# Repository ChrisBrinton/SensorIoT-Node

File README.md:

# SensorIoT-Node (Deprecated)

> **This repository has been consolidated into [SensorIoT-GW](https://github.com/ChrisBrinton/SensorIoT-GW).**
>
> All sensor node firmware and PCB designs now live under `firmware/node/` and `PCBs/node/` in the consolidated repo.
> This repository is kept for historical reference only.

## Original Description
# SensorIoT-Node
The sensor nodes for the SensorIoT environment

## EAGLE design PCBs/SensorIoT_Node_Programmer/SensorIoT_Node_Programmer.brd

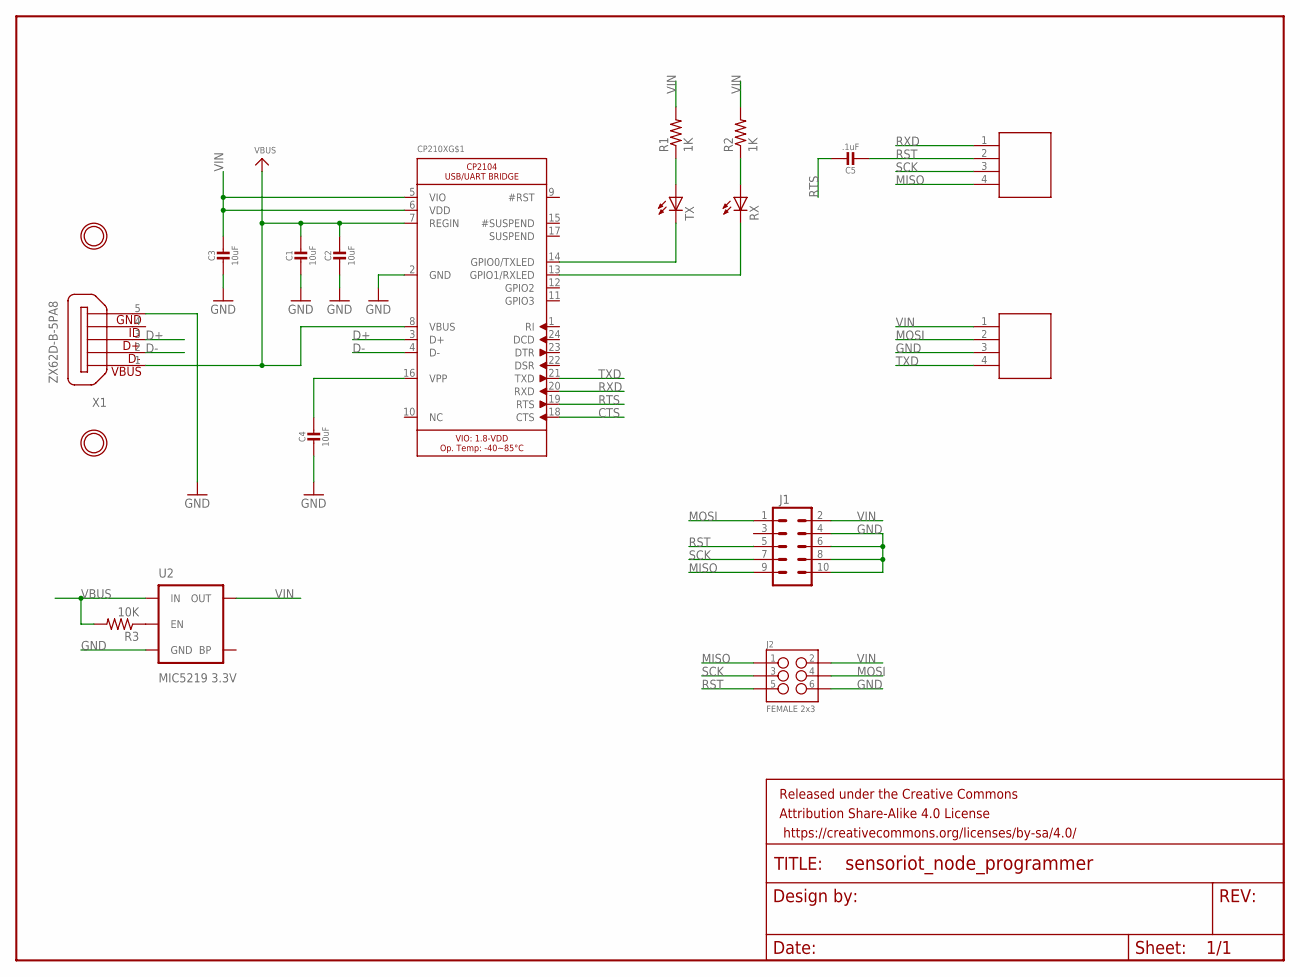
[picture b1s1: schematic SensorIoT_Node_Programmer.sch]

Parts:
C1, C2, C3, C4: 10uF; _0805
C5: .1uF; _0805
CP210X: CP2104; QFN24_4MM_SMSC
FRAME1: FRAME-LETTER; CREATIVE_COMMONS
J1: M05X2PTH; AVR_ICSP
J2: FEMALE 2x3; 2X3
R1, R2: 1K; 0805
R3: 10K; 0805
RX: LEDCHIP-LED0805; CHIP-LED0805
TX: LEDCHIP-LED0805; CHIP-LED0805
U2: MIC5219 3.3V; SOT23-5
U$2, U$3: MOUNTINGHOLE2.0; MOUNTINGHOLE_2.0_PLATED
U$4, U$5: 4X.1IN_POGO_PIN
X1: ZX62D-B-5PA8

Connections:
CTS: CP210X.18 (CTS)
D+: CP210X.3 (D+), X1.3
D-: CP210X.4 (D-), X1.2
GND: C1.2, C2.2, C3.2, C4.2, CP210X.2 (GND), J1.4, J1.6, J1.8, J1.10, J2.6, U2.2 (GND), U$5.3, X1.5
MISO: J1.9, J2.1, U$4.4
MOSI: J1.1, J2.4, U$5.2
unnamed: C4.1, CP210X.16 (VPP)
unnamed: CP210X.14 (GPIO0/TXLED), TX.C
unnamed: R3.1, U2.3 (EN)
unnamed: CP210X.13 (GPIO1/RXLED), RX.C
unnamed: R1.1, TX.A
unnamed: R2.1, RX.A
RST: C5.2, J1.5, J2.5, U$4.2
RTS: C5.1, CP210X.19 (RTS)
RXD: CP210X.20 (RXD), U$4.1
SCK: J1.7, J2.3, U$4.3
TP: CP210X.THERM (TP)
TXD: CP210X.21 (TXD), U$5.4
VBUS: C1.1, C2.1, CP210X.7 (REGIN), CP210X.8 (VBUS), R3.2, U2.1 (IN), X1.1
VIN: C3.1, CP210X.5 (VIO), CP210X.6 (VDD), J1.2, J2.2, R1.2, R2.2, U2.5 (OUT), U$5.1

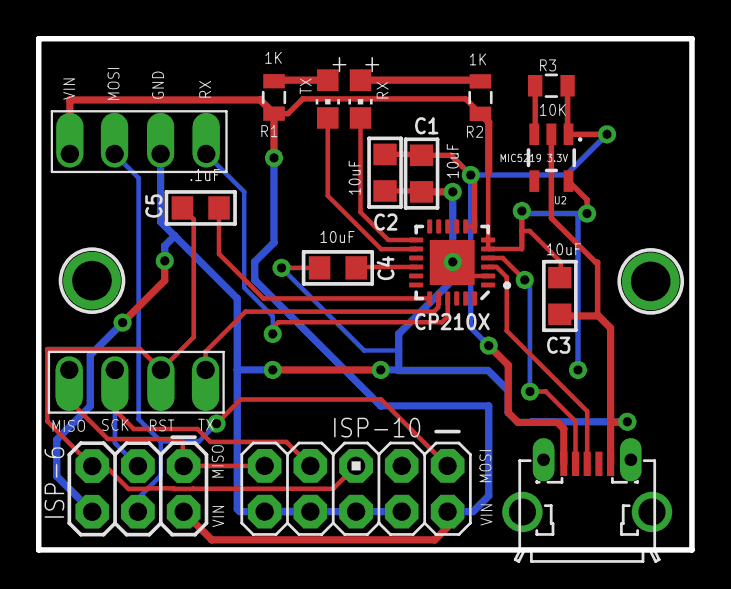
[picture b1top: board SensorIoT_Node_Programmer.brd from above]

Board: 2 copper layers, 36.3 x 28.4 mm, 20 parts (0 on the bottom side), 18 nets.

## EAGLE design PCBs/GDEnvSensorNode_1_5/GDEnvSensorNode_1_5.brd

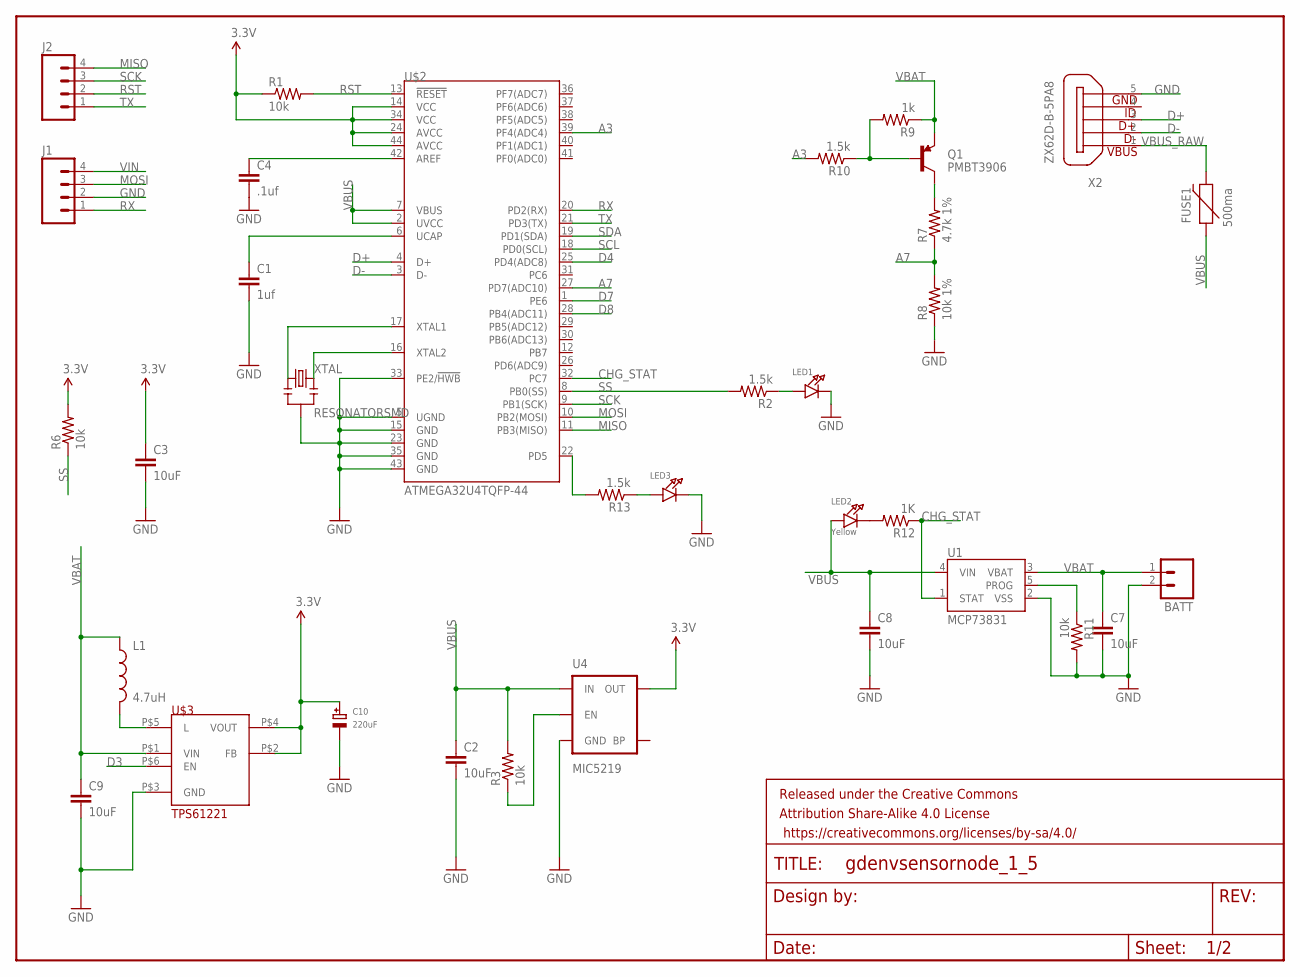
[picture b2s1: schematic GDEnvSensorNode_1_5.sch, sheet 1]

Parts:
BATT: M02JST-PTH-2; JST-2-PTH
C1: 1uf; 0805
C2, C3, C7, C8, C9: 10uF; 0805
C4: .1uf; 0805
C10: 220uF; EIA3528-21/B-R
FRAME1: FRAME-LETTER; CREATIVE_COMMONS
FUSE1: 500ma; PTC-1206
J1, J2: M04PTH; 1X04
L1: 4.7uH; 1210
LED1, LED3: LED0805; CHIPLED_0805
LED2: Yellow; CHIPLED_0805
Q1: PMBT3906; SOT23-3
R1, R3, R6, R11: 10k; 0805
R2, R10, R13: 1.5k; 0805
R7: 4.7k 1%; 0805
R8: 10k 1%; 0805
R9: 1k; 0805
R12: 1K; 0805
U1: MCP73831; SOT23-5
U4: MIC5219; SOT23-5
U$2: ATMEGA32U4TQFP-44; TQFP44
U$3: TPS61221
X2: ZX62D-B-5PA8
XTAL: RESONATORSMD; RESONATOR-SMD

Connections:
A3: R10.2, U$2.39 (PF4(ADC4))
A7: R7.1, R8.2, U$2.27 (PD7(ADC10))
CHG_STAT: R12.1, U1.1 (STAT), U$2.32 (PC7)
D3: U$3.P$6 (EN)
D4: U$2.25 (PD4(ADC8)); also elsewhere on the board
D7: U$2.1 (PE6); also elsewhere on the board
D8: U$2.28 (PB4(ADC11)); also elsewhere on the board
D+: U$2.4 (D+), X2.3
D-: U$2.3 (D-), X2.2
GND: BATT.2, C1.2, C2.2, C3.2, C4.2, C7.2, C8.2, C9.2, C10.-, J1.2, LED1.C, LED3.C, R8.1, R11.2, U1.2 (VSS), U4.2 (GND), U$2.5 (UGND), U$2.15 (GND), U$2.23 (GND), U$2.33 (PE2/!HWB), U$2.35 (GND), U$2.43 (GND), U$3.P$3 (GND), X2.5, XTAL.2; also elsewhere on the board
L: L1.2, U$3.P$5 (L)
MISO: J2.4, U$2.11 (PB3(MISO)); also elsewhere on the board
MOSI: J1.3, U$2.10 (PB2(MOSI)); also elsewhere on the board
unnamed: U$2.16 (XTAL2), XTAL.3
unnamed: U$2.17 (XTAL1), XTAL.1
unnamed: LED1.A, R2.1
unnamed: LED2.C, R12.2
unnamed: C4.1, U$2.42 (AREF)
unnamed: LED3.A, R13.1
unnamed: R3.1, U4.3 (EN)
unnamed: Q1.1 (B), R9.2, R10.1
unnamed: Q1.3 (C), R7.2
unnamed: R13.2, U$2.22 (PD5)
unnamed: R11.1, U1.5 (PROG)
unnamed: C1.1, U$2.6 (UCAP)
RST: J2.2, R1.2, U$2.13 (!RESET)
RX: J1.1, U$2.20 (PD2(RX))
SCK: J2.3, U$2.9 (PB1(SCK)); also elsewhere on the board
SCL: U$2.18 (PD0(SCL)); also elsewhere on the board
SDA: U$2.19 (PD1(SDA)); also elsewhere on the board
SS: R2.2, R6.1, U$2.8 (PB0(SS))
TX: J2.1, U$2.21 (PD3(TX))
VBAT: BATT.1, C7.1, C9.1, L1.1, Q1.2 (E), R9.1, U1.3 (VBAT), U$3.P$1 (VIN)
VBUS: C2.1, C8.1, FUSE1.1, LED2.A, R3.2, U1.4 (VIN), U4.1 (IN), U$2.2 (UVCC), U$2.7 (VBUS)
VBUS_RAW: FUSE1.2, X2.1
VIN: J1.4

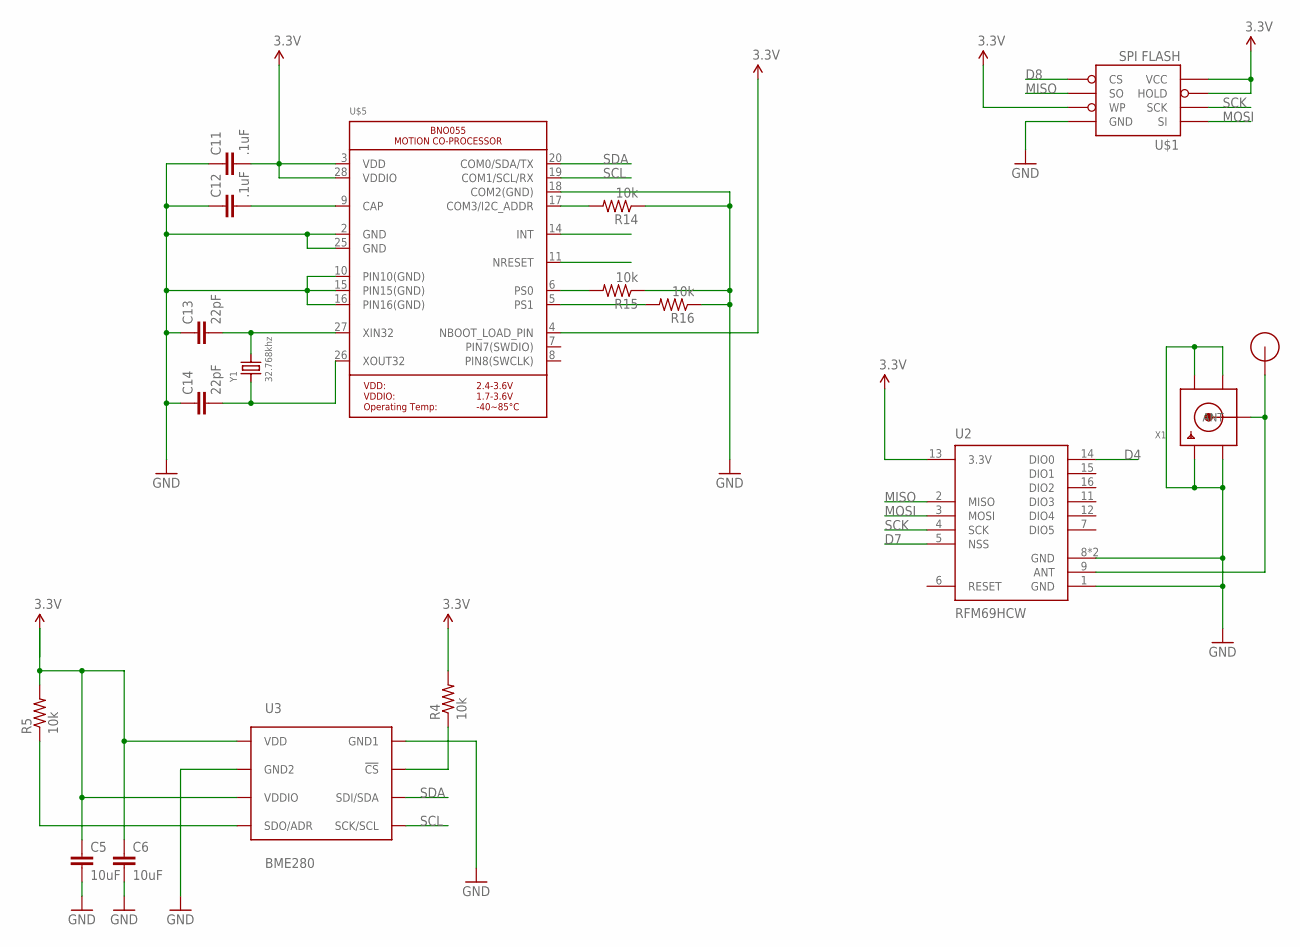
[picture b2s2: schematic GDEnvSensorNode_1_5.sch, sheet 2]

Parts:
C5, C6: 10uF; 0805
C11, C12: .1uF; 0805
C13, C14: 22pF; 0805
R4, R5, R14, R15, R16: 10k; 0805
U2: RFM69HCW; RFM69HCW-XXXS2
U3: BME280; BME280_LGA
U$1: SPI FLASH; SO08
U$4: RFM12B_ANTENNA; RFM12B-ANTENNA
U$5: MICROBUILDER_BNO055
X1: SMACONNECTOR_EDGE_UFL; SMA_EDGELAUNCH_UFL
Y1: 32.768khz; CRYSTAL_8X3.8

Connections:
ANT: U2.9 (ANT), U$4.P$1, X1.P (ANT)
D4: U2.14 (DIO0); also elsewhere on the board
D7: U2.5 (NSS); also elsewhere on the board
D8: U$1.1_CS (CS); also elsewhere on the board
GND: C5.2, C6.2, C11.1, C12.1, C13.1, C14.1, R14.1, R15.1, R16.1, U2.1 (GND), U2.8 (GND), U2.10 (GND), U3.P$1 (GND1), U3.P$7 (GND2), U$1.4_GND (GND), U$5.2 (GND), U$5.10 (PIN10(GND)), U$5.15 (PIN15(GND)), U$5.16 (PIN16(GND)), U$5.18 (COM2(GND)), U$5.25 (GND), X1.GND@1 (GND1), X1.GND@2 (GND2), X1.GND@3 (GND3), X1.GND@4 (GND4); also elsewhere on the board
MISO: U2.2 (MISO), U$1.2_SO (SO); also elsewhere on the board
MOSI: U2.3 (MOSI), U$1.5_SI (SI); also elsewhere on the board
unnamed: R4.1, U3.P$2 (!CS)
unnamed: C12.2, U$5.9 (CAP)
unnamed: C5.1, C6.1, R5.2, U3.P$6 (VDDIO), U3.P$8 (VDD)
unnamed: R5.1, U3.P$5 (SDO/ADR)
unnamed: C13.2, U$5.27 (XIN32), Y1.P$4 (2)
unnamed: C14.2, U$5.26 (XOUT32), Y1.P$1 (1)
unnamed: R14.2, U$5.17 (COM3/I2C_ADDR)
unnamed: R15.2, U$5.6 (PS0)
unnamed: R16.2, U$5.5 (PS1)
SCK: U2.4 (SCK), U$1.6_SCK (SCK); also elsewhere on the board
SCL: U3.P$4 (SCK/SCL), U$5.19 (COM1/SCL/RX); also elsewhere on the board
SDA: U3.P$3 (SDI/SDA), U$5.20 (COM0/SDA/TX); also elsewhere on the board

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
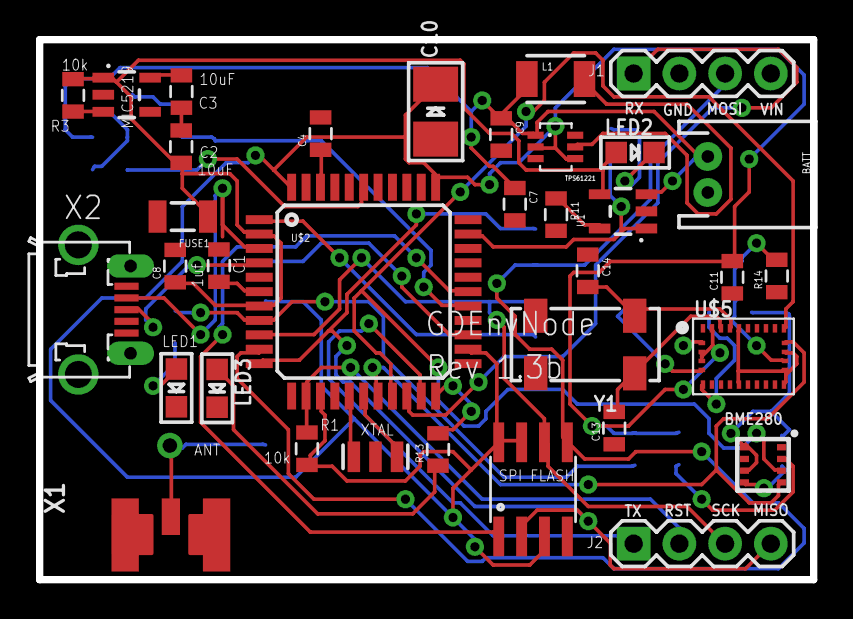
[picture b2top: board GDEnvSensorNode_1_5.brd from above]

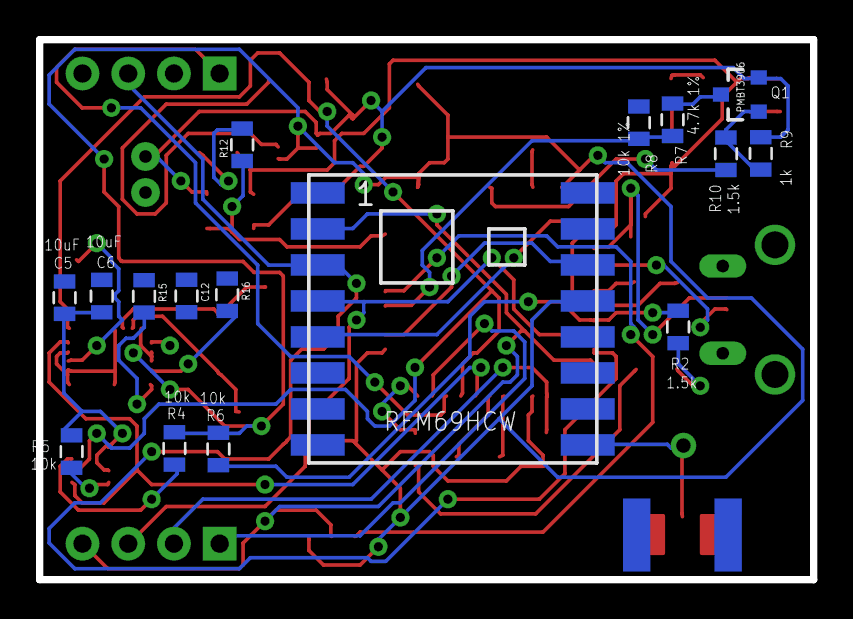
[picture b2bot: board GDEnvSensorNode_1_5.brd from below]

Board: 2 copper layers, 43.0 x 30.0 mm, 53 parts (16 on the bottom side), 46 nets.

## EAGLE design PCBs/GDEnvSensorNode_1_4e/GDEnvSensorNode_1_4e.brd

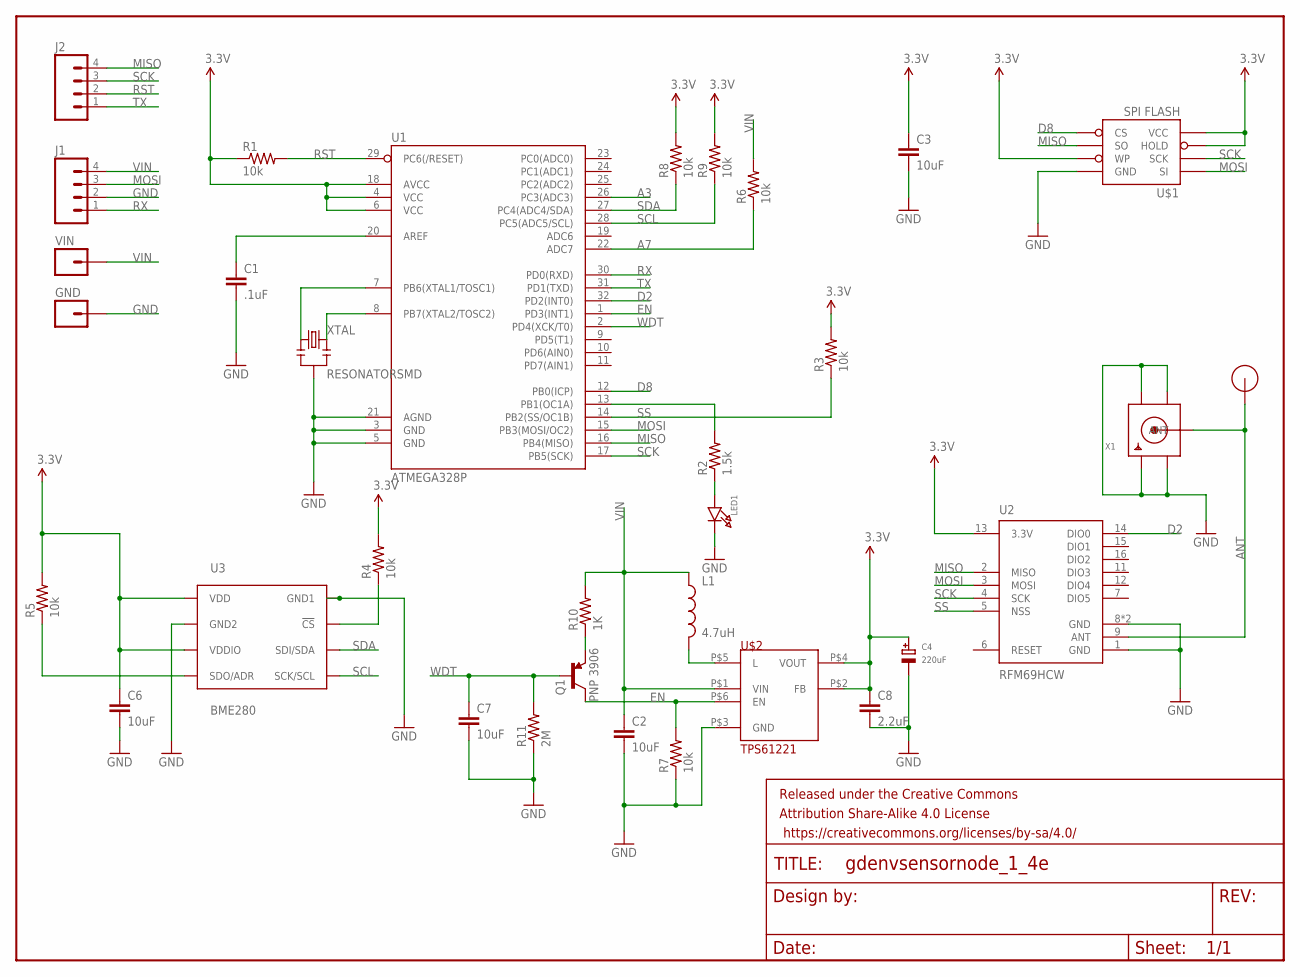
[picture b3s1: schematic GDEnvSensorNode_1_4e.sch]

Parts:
C1: .1uF; 0805
C2, C3, C6, C7: 10uF; 0805
C4: 220uF; EIA7343-31/D-R
C8: 2.2uF; 0805
FRAME1: FRAME-LETTER; CREATIVE_COMMONS
GND: M01PTH_2MM; 1X01_2MM
J1, J2: M04PTH; 1X04
L1: 4.7uH; 1210
LED1: LED0805; CHIPLED_0805
Q1: PNP 3906; SOT23-3
R1, R3, R4, R5, R6, R7, R8, R9: 10k; 0805
R2: 1.5k; 0805
R10: 1K; R0805
R11: 2M; R0805
U1: ATMEGA328P; TQFP32-08
U2: RFM69HCW; RFM69HCW-XXXS2
U3: BME280; BME280_LGA
U$1: SPI FLASH; SO08
U$2: TPS61221
U$4: RFM12B_ANTENNA; RFM12B-ANTENNA
VIN: M01PTH_2MM; 1X01_2MM
X1: SMACONNECTOR_EDGE_UFL; SMA_EDGELAUNCH_UFL
XTAL: RESONATORSMD; RESONATOR-SMD

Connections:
3.3V: C3.1, C4.+, C6.1, C8.1, R1.1, R3.2, R4.2, R5.2, R8.2, R9.2, U1.4 (VCC), U1.6 (VCC), U1.18 (AVCC), U2.13 (3.3V), U3.P$6 (VDDIO), U3.P$8 (VDD), U$1.3_WP (WP), U$1.7_HOLD (HOLD), U$1.8_VCC (VCC), U$2.P$2 (FB), U$2.P$4 (VOUT)
A3: U1.26 (PC3(ADC3))
A7: R6.1, U1.22 (ADC7)
ANT: U2.9 (ANT), U$4.P$1, X1.P (ANT)
D2: U1.32 (PD2(INT0)), U2.14 (DIO0)
D8: U1.12 (PB0(ICP)), U$1.1_CS (CS)
EN: Q1.3 (C), R7.2, U1.1 (PD3(INT1)), U$2.P$6 (EN)
GND: C1.2, C2.2, C3.2, C4.-, C6.2, C7.2, C8.2, GND.1, J1.2, LED1.C, R7.1, R11.1, U1.3 (GND), U1.5 (GND), U1.21 (AGND), U2.1 (GND), U2.8 (GND), U2.10 (GND), U3.P$1 (GND1), U3.P$7 (GND2), U$1.4_GND (GND), U$2.P$3 (GND), X1.GND@1 (GND1), X1.GND@2 (GND2), X1.GND@3 (GND3), X1.GND@4 (GND4), XTAL.2
L: L1.2, U$2.P$5 (L)
MISO: J2.4, U1.16 (PB4(MISO)), U2.2 (MISO), U$1.2_SO (SO)
MOSI: J1.3, U1.15 (PB3(MOSI/OC2)), U2.3 (MOSI), U$1.5_SI (SI)
unnamed: U1.8 (PB7(XTAL2/TOSC2)), XTAL.3
unnamed: U1.7 (PB6(XTAL1/TOSC1)), XTAL.1
unnamed: LED1.A, R2.1
unnamed: Q1.2 (E), R10.1
unnamed: R4.1, U3.P$2 (!CS)
unnamed: R2.2, U1.13 (PB1(OC1A))
unnamed: C1.1, U1.20 (AREF)
unnamed: R5.1, U3.P$5 (SDO/ADR)
RST: J2.2, R1.2, U1.29 (PC6(/RESET))
RX: J1.1, U1.30 (PD0(RXD))
SCK: J2.3, U1.17 (PB5(SCK)), U2.4 (SCK), U$1.6_SCK (SCK)
SCL: R9.1, U1.28 (PC5(ADC5/SCL)), U3.P$4 (SCK/SCL)
SDA: R8.1, U1.27 (PC4(ADC4/SDA)), U3.P$3 (SDI/SDA)
SS: R3.1, U1.14 (PB2(SS/OC1B)), U2.5 (NSS)
TX: J2.1, U1.31 (PD1(TXD))
VIN: C2.1, J1.4, L1.1, R6.2, R10.2, U$2.P$1 (VIN), VIN.1
WDT: C7.1, Q1.1 (B), R11.2, U1.2 (PD4(XCK/T0))

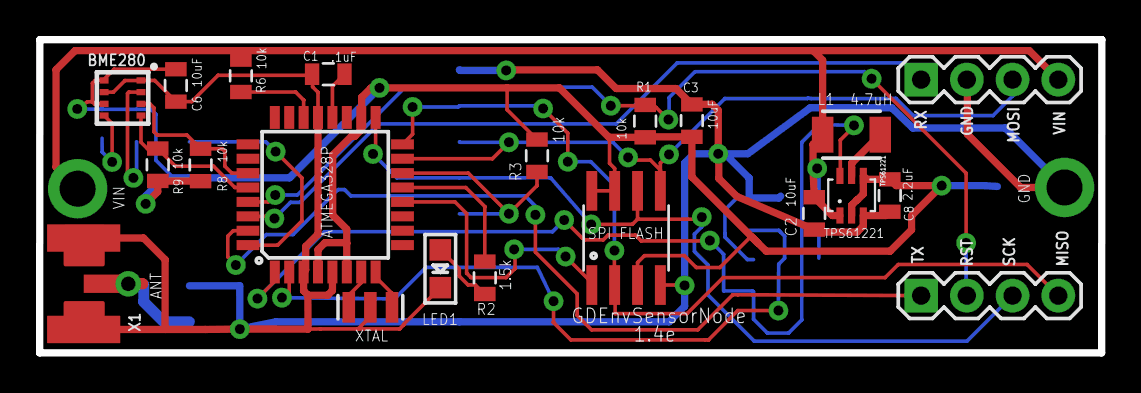
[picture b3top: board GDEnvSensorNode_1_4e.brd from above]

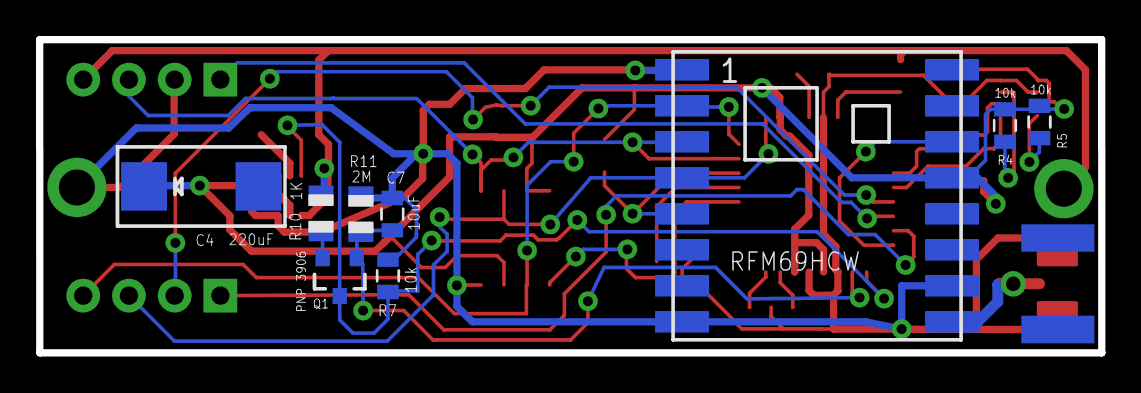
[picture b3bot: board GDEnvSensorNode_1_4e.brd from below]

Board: 2 copper layers, 59.0 x 17.4 mm, 34 parts (9 on the bottom side), 27 nets.

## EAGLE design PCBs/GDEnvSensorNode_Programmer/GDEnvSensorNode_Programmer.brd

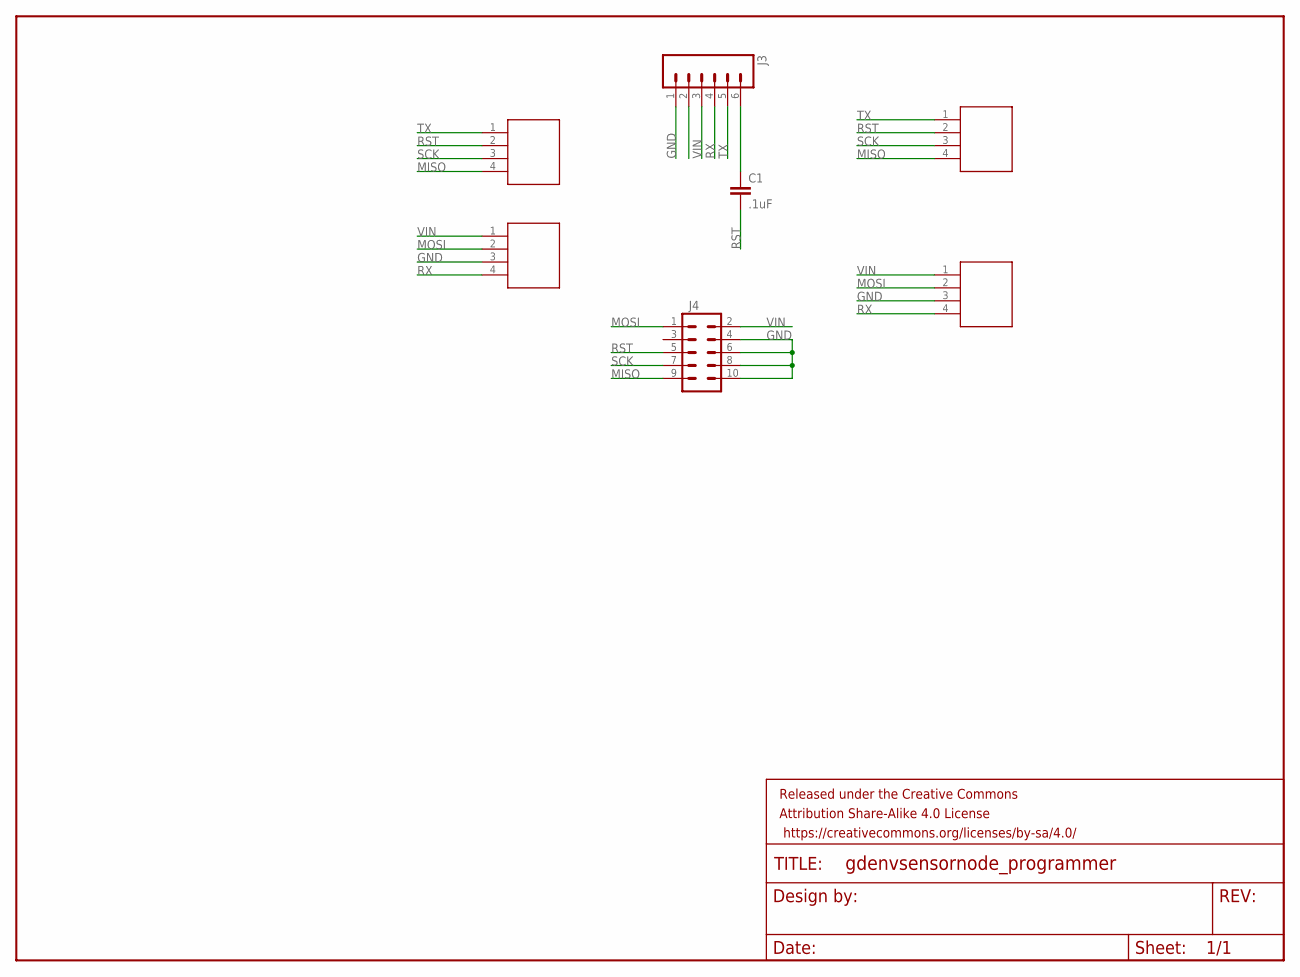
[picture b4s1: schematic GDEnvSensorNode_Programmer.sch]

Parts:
C1: .1uF; 0805
FRAME1: FRAME-LETTER; CREATIVE_COMMONS
J1, J2, J5, J6: 4X.1IN_POGO_PIN
J3: M06LONGPADS; 1X06_LONGPADS
J4: M05X2PTH; AVR_ICSP

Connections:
GND: J2.3, J3.1, J4.4, J4.6, J4.8, J4.10, J6.3
MISO: J1.4, J4.9, J5.4
MOSI: J2.2, J4.1, J6.2
unnamed: C1.1, J3.6
RST: C1.2, J1.2, J4.5, J5.2
RX: J2.4, J3.4, J6.4
SCK: J1.3, J4.7, J5.3
TX: J1.1, J3.5, J5.1
VIN: J2.1, J3.3, J4.2, J6.1

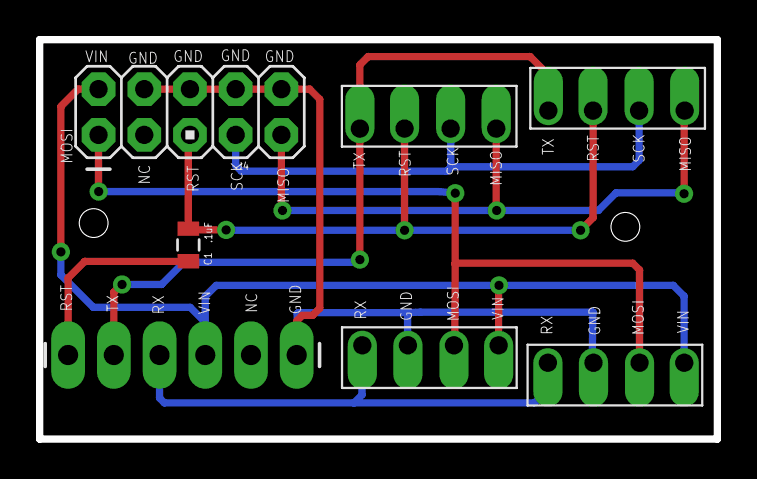
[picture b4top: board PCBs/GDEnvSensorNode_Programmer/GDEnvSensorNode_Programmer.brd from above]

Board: 2 copper layers, 37.6 x 22.2 mm, 8 parts (0 on the bottom side), 9 nets.

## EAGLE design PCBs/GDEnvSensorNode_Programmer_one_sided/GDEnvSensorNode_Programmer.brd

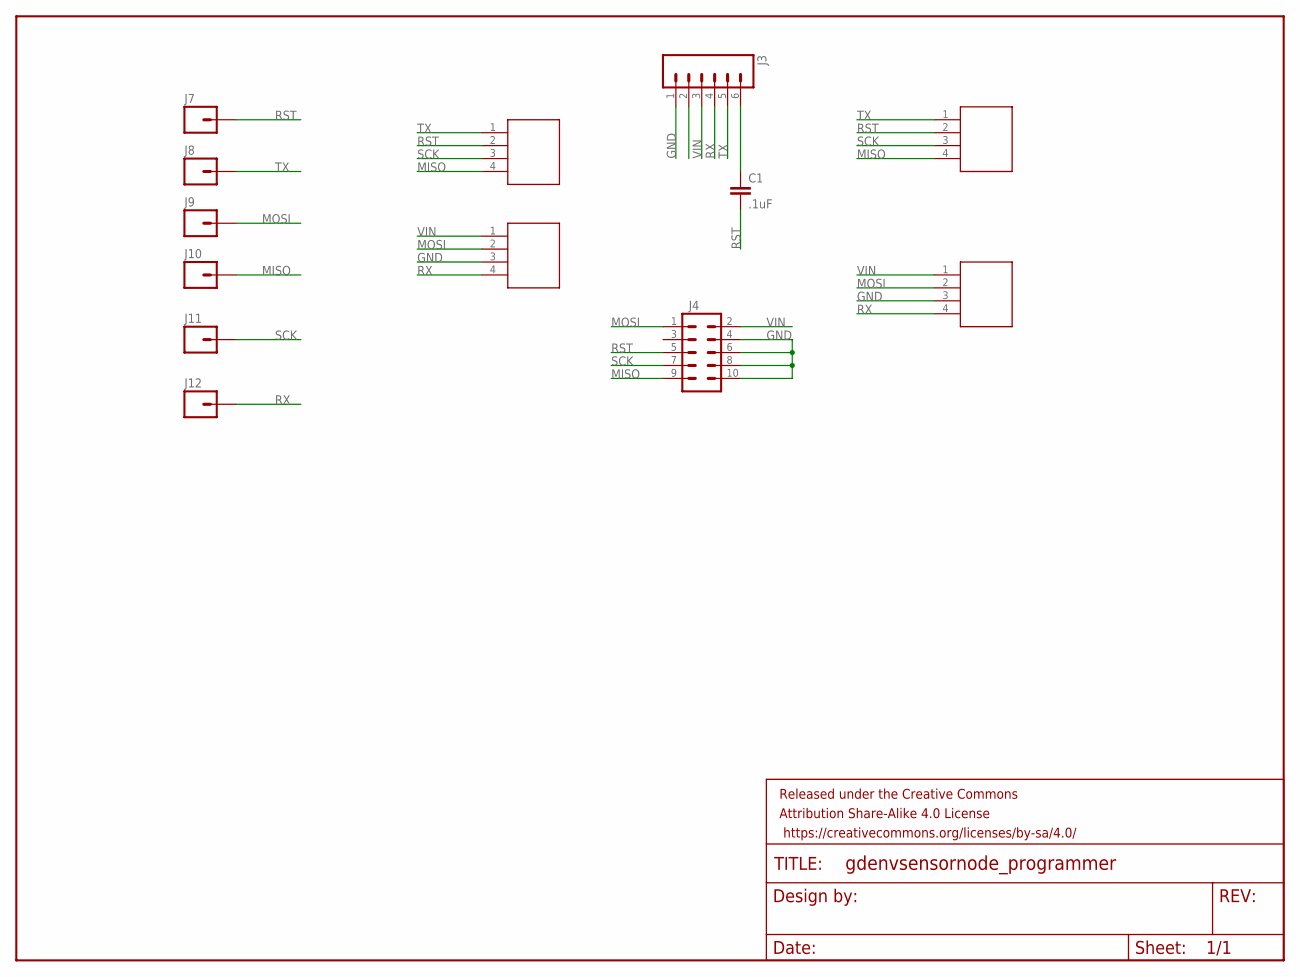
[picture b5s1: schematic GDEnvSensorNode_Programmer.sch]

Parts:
C1: .1uF; 0805
FRAME1: FRAME-LETTER; CREATIVE_COMMONS
J1, J2, J5, J6: 4X.1IN_POGO_PIN
J3: M06LONGPADS; 1X06_LONGPADS
J4: M05X2PTH; AVR_ICSP
J7, J8, J9, J10, J11, J12: M01PTH; 1X01

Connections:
GND: J2.3, J3.1, J4.4, J4.6, J4.8, J4.10, J6.3
MISO: J1.4, J4.9, J5.4, J10.1
MOSI: J2.2, J4.1, J6.2, J9.1
unnamed: C1.1, J3.6
RST: C1.2, J1.2, J4.5, J5.2, J7.1
RX: J2.4, J3.4, J6.4, J12.1
SCK: J1.3, J4.7, J5.3, J11.1
TX: J1.1, J3.5, J5.1, J8.1
VIN: J2.1, J3.3, J4.2, J6.1

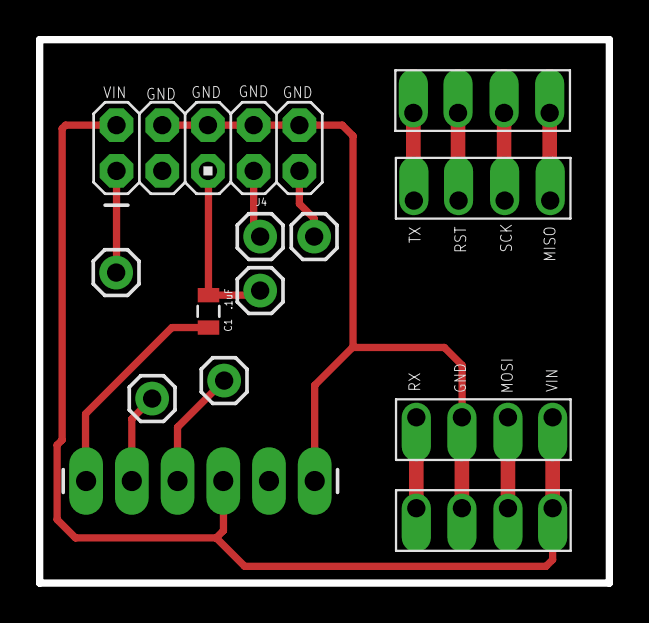
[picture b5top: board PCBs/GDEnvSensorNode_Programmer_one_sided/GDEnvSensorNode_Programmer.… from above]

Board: 2 copper layers, 31.6 x 30.2 mm, 14 parts (0 on the bottom side), 9 nets.

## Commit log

2018-06-01 initial push
2019-06-20 bring PCS up to date to 1.4h
2019-06-20 Initial release of controllable boost power node
2019-10-18 Reorg and RFM95 support
2026-03-19 Add deprecation notice — code moved to SensorIoT-GW repo
    https://claude.ai/code/session_0171vFeZAqu7LSvjEKnyn65i

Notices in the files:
parts and their libraries:
SparkFun-Capacitors: Licensing: Creative Commons ShareAlike 4.0 International - https://creativecommons.org/licenses/by-sa/4.0
SparkFun-Aesthetics: Released under the Creative Commons Attribution Share-Alike 4.0 License
SparkFun-Aesthetics: https://creativecommons.org/licenses/by-sa/4.0
